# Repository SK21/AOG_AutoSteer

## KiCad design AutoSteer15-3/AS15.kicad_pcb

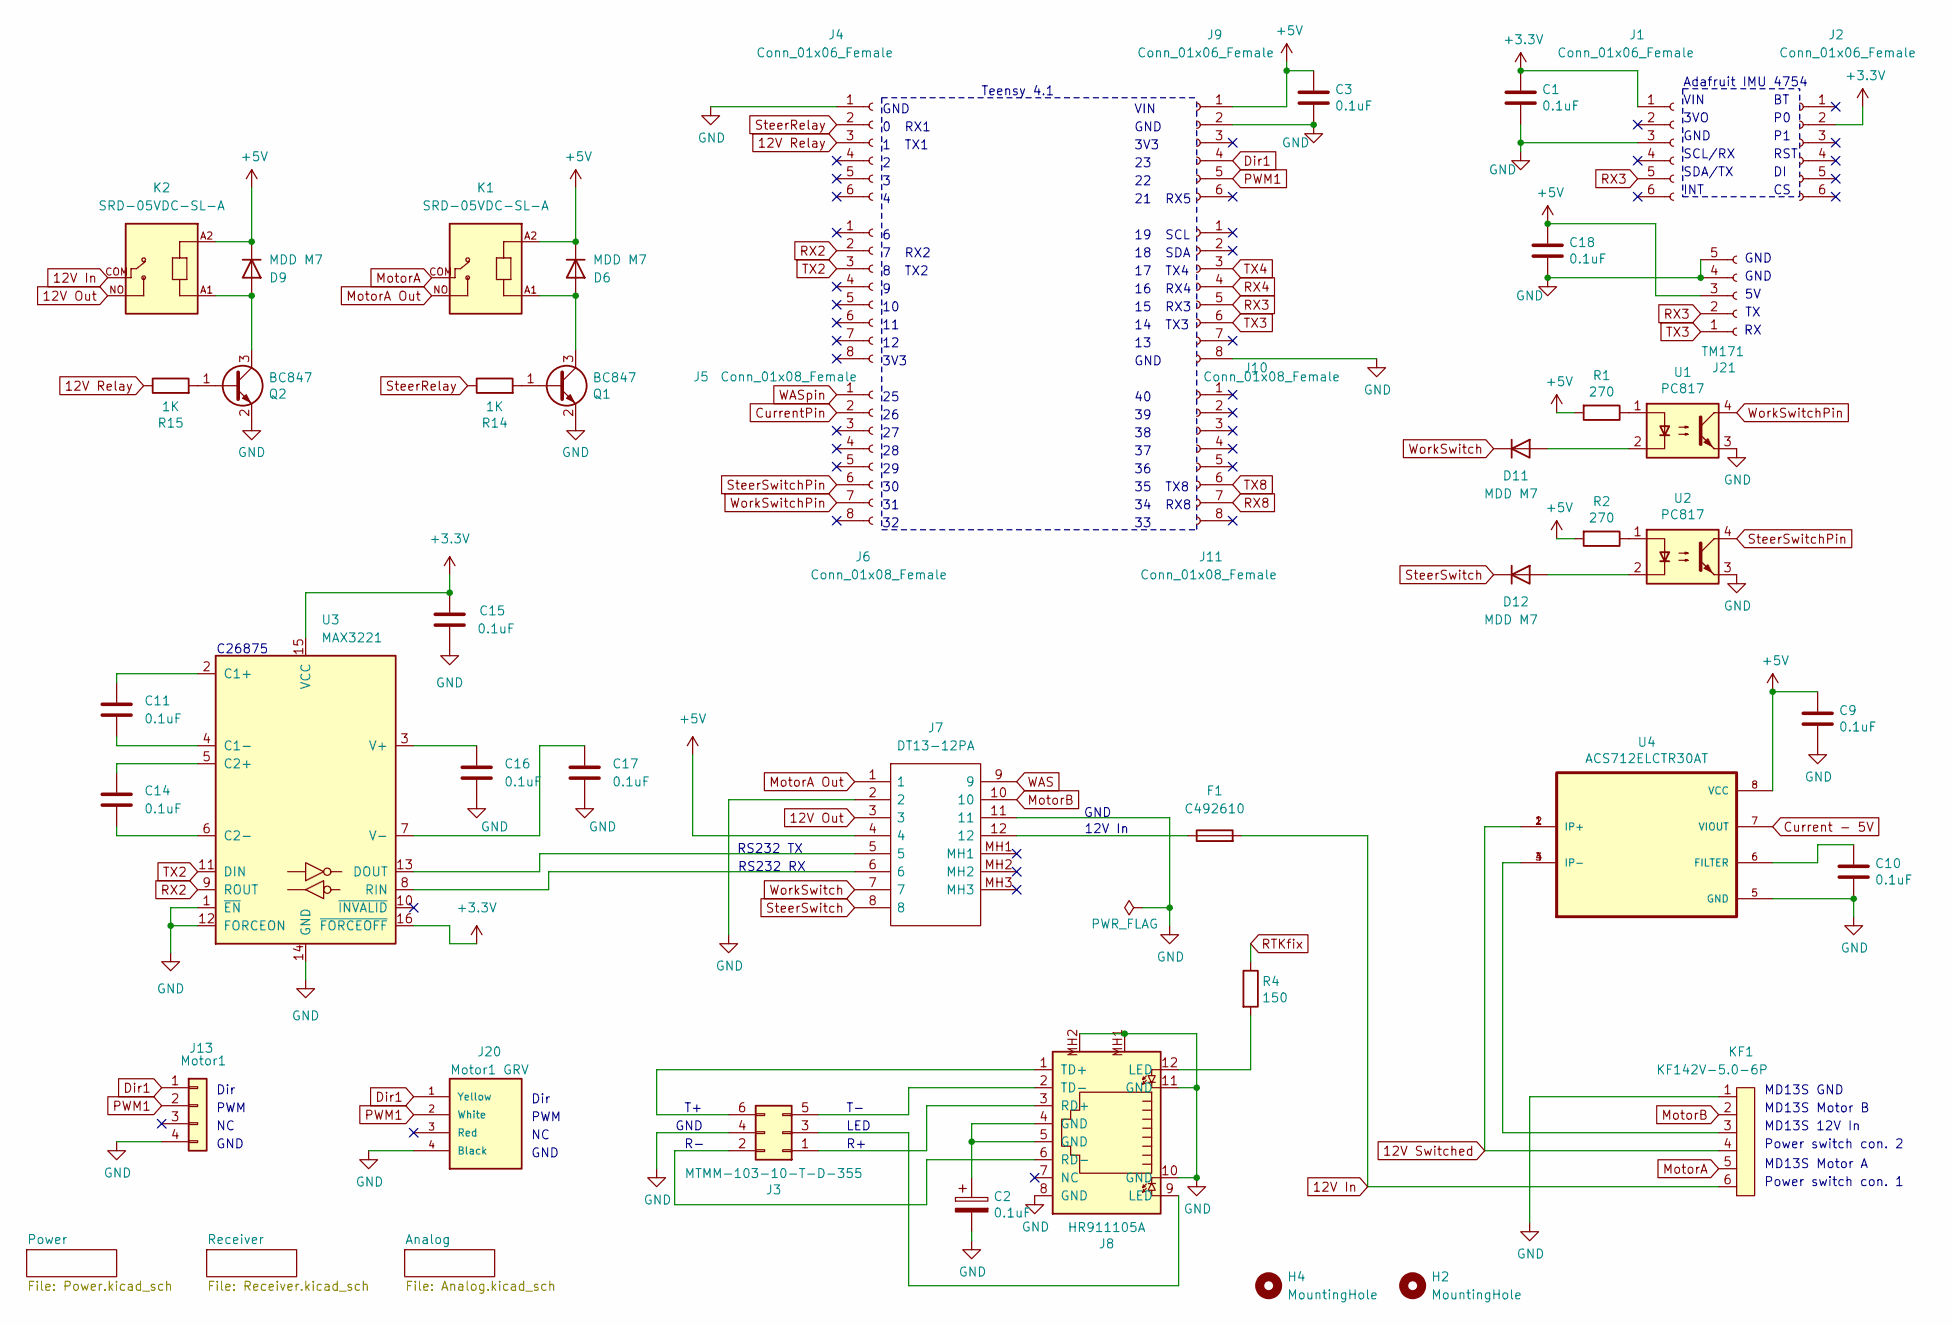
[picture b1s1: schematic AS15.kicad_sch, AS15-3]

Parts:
C1, C2, C3, C9, C10, C11, C14, C15, C16, C17, C18: 0.1uF; C_0805_2012Metric
D6, D9, D11, D12: MDD M7; D_SMA
F1: C492610; Fuse_Holder_C492610
H2, H4: MountingHole; MountingHole_4.3mm_M4
J1, J2, J4, J9: Conn_01x06_Female; PinSocket_1x06_P2.54mm_Vertical
J3: MTMM-103-10-T-D-355; PinHeader_2x03_P2.00mm_Vertical
J5, J6, J10, J11: Conn_01x08_Female; PinSocket_1x08_P2.54mm_Vertical
J7: DT13-12PA; DT1312PA; Manufacturer_Part_Number DT13-12PA; Mouser Part Number 571-DT13-12PA
J8: HR911105A
J13: Motor1; Molex_KK-254_AE-6410-04A_1x04_P2.54mm_Vertical
J20: Motor1 GRV; Grove
J21: TM171; PinSocket_1x05_P2.54mm_Vertical
K1, K2: SRD-05VDC-SL-A; RELAY_SRD-05VDC-SL-A
KF1: KF142V-5.0-6P; KF142V-5.08-6P
Q1, Q2: BC847; SOT-23
R1, R2: 270; R_0603_1608Metric
R4: 150; R_0603_1608Metric
R14, R15: 1K; R_0603_1608Metric
U1, U2: PC817; SMD-4_4.6x7.62mm_P2.54mm
U3: MAX3221; SOP65P777X199-16N
U4: ACS712ELCTR30AT; SOIC127P600X175-8N; PARTREV 1.0

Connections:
12V In: F1.2, K2.COM, KF1.6
12V Out: J7.3, K2.NO
12V Relay: J4.3, R15.1
12V Switched: KF1.4, U4.1 (IP+), U4.2 (IP+); also elsewhere on the board
+3.3V: C1.1, C15.1, J1.1, J2.2, U3.15 (VCC), U3.16 (~FORCEOFF); also elsewhere on the board
+5V: C3.1, C9.1, C18.1, D6.1 (K), D9.1 (K), J7.4, J9.1, J21.3, K1.A2, K2.A2, R1.2, R2.2, U4.8 (VCC); also elsewhere on the board
Current - 5V: U4.7 (VIOUT); also elsewhere on the board
CurrentPin: J6.2; also elsewhere on the board
Dir1: J9.4, J13.1, J20.1 (Yellow)
GND: C1.2, C2.2, C3.2, C9.2, C10.2, C15.2, C16.2, C17.2, C18.2, J1.3, J3.4, J4.1, J7.2, J7.11, J8.8 (GND), J8.10 (GND), J8.11 (GND), J8.MH1, J8.MH2, J9.2, J10.8, J13.4, J20.4 (Black), J21.4, J21.5, KF1.1, Q1.2 (E), Q2.2 (E), U1.3, U2.3, U3.1 (~EN), U3.12 (FORCEON), U3.14 (GND), U4.5 (GND); also elsewhere on the board
MotorA: K1.COM, KF1.5
MotorA Out: J7.1, K1.NO
MotorB: J7.10, KF1.2
unnamed: C2.1, J8.4 (GND), J8.5 (GND)
unnamed: D6.2 (A), K1.A1, Q1.3 (C)
unnamed: D9.2 (A), K2.A1, Q2.3 (C)
unnamed: D11.2 (A), U1.2
unnamed: D12.2 (A), U2.2
unnamed: F1.1, J7.12
unnamed: J3.1, J8.3 (RD+)
unnamed: J3.2, J8.6 (RD-)
unnamed: J3.3, J8.9 (LED)
unnamed: J3.5, J8.2 (TD-)
unnamed: J3.6, J8.1 (TD+)
unnamed: J8.12 (LED), R4.2
unnamed: KF1.3, U4.3 (IP-), U4.4 (IP-)
unnamed: Q1.1 (B), R14.2
unnamed: Q2.1 (B), R15.2
unnamed: R1.1, U1.1
unnamed: R2.1, U2.1
unnamed: C11.1, U3.2 (C1+)
unnamed: C11.2, U3.4 (C1-)
unnamed: C14.1, U3.5 (C2+)
unnamed: C14.2, U3.6 (C2-)
unnamed: J7.5, U3.13 (DOUT)
unnamed: J7.6, U3.8 (RIN)
unnamed: C16.1, U3.3 (V+)
unnamed: C17.1, U3.7 (V-)
unnamed: C10.1, U4.6 (FILTER)
PWM1: J9.5, J13.2, J20.2 (White)
RTKfix: R4.1; also elsewhere on the board
RX2: J5.2, U3.9 (ROUT)
RX3: J1.5, J10.5, J21.2
RX4: J10.4; also elsewhere on the board
RX8: J11.7; also elsewhere on the board
SteerRelay: J4.2, R14.1
SteerSwitch: D12.1 (K), J7.8
SteerSwitchPin: J6.6, U2.4
TX2: J5.3, U3.11 (DIN)
TX3: J10.6, J21.1
TX4: J10.3; also elsewhere on the board
TX8: J11.6; also elsewhere on the board
WAS: J7.9; also elsewhere on the board
WASpin: J6.1; also elsewhere on the board
WorkSwitch: D11.1 (K), J7.7
WorkSwitchPin: J6.7, U1.4

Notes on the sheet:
3V3
GND
RS232 TX
C26875
7 RX2
19 SCL
Teensy 4.1
MD13S Motor B
LED
8 TX2
35 TX8
Dir
16 RX4
SCL/RX
MD13S GND
14 TX3
VIN
17 TX4
RST
PWM
3VO
12V In
Power switch con. 1
MD13S Motor A
MD13S 12V In
34 RX8
Power switch con. 2
1 TX1
RS232 RX
18 SDA
INT
0 RX1
SDA/TX
21 RX5
15 RX3
Adafruit IMU 4754

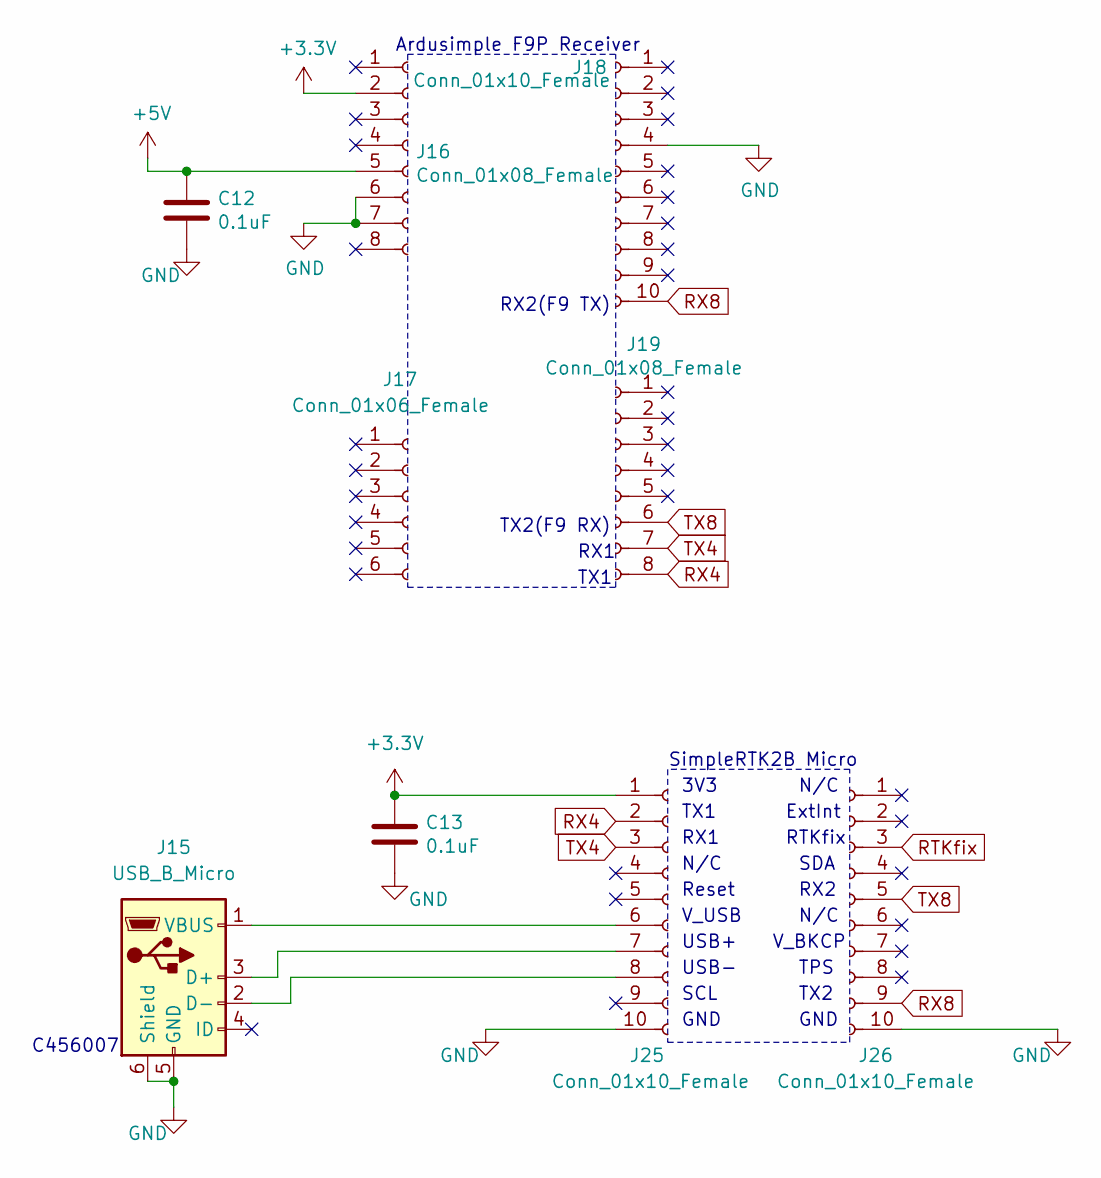
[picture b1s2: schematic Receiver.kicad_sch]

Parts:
C12, C13: 0.1uF; C_0805_2012Metric
J15: USB_B_Micro; USB_Micro-B_Wuerth_614105150721_Vertical
J16, J19: Conn_01x08_Female; PinSocket_1x08_P2.54mm_Vertical
J17: Conn_01x06_Female; PinSocket_1x06_P2.54mm_Vertical
J18: Conn_01x10_Female; PinSocket_1x10_P2.54mm_Vertical
J25, J26: Conn_01x10_Female; PinSocket_1x10_P2.00mm_Vertical

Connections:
+3.3V: C13.1, J16.2, J25.1; also elsewhere on the board
+5V: C12.1, J16.5; also elsewhere on the board
GND: C12.2, C13.2, J15.5 (GND), J15.6 (Shield), J16.6, J16.7, J18.4, J25.10, J26.10; also elsewhere on the board
unnamed: J15.3 (D+), J25.7
unnamed: J15.2 (D-), J25.8
unnamed: J15.1 (VBUS), J25.6
RTKfix: J26.3; also elsewhere on the board
RX4: J19.8, J25.2; also elsewhere on the board
RX8: J18.10, J26.9; also elsewhere on the board
TX4: J19.7, J25.3; also elsewhere on the board
TX8: J19.6, J26.5; also elsewhere on the board

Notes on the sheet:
RX1
3V3
TX1
SCL
RX2(F9 TX)
GND
N/C
USB-
TPS
SDA
TX2
V_USB
V_BKCP
RX2
C456007
ExtInt
Reset
Ardusimple F9P Receiver
SimpleRTK2B Micro
RTKfix
TX2(F9 RX)
USB+

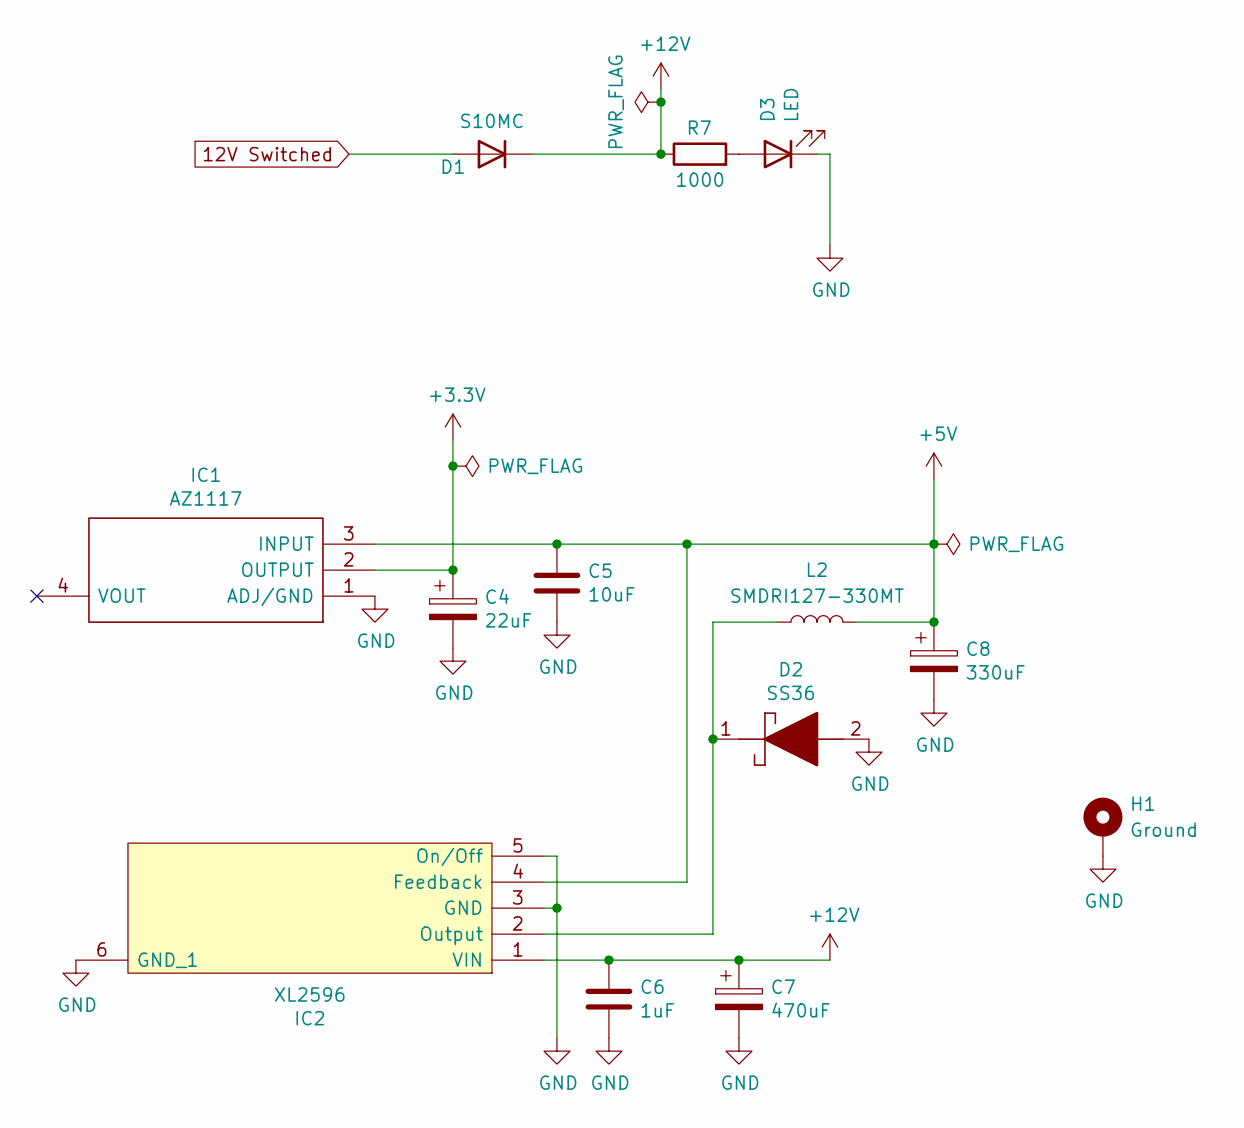
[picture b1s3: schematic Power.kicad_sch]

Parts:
C4: 22uF; C_0805_2012Metric
C5: 10uF; C_0805_2012Metric
C6: 1uF; C_0805_2012Metric
C7: 470uF; CP_Elec_10x10.5
C8: 330uF; CP_Elec_10x10.5
D1: S10MC; D_SMC_larger_pads
D2: SS36; SMA(DO-214AC)
D3: LED; LED_0805_2012Metric
H1: Ground; MountingHole_2.2mm_M2_DIN965_Pad
IC1: AZ1117; SOT-223
IC2: XL2596; TO263-5L
L2: SMDRI127-330MT; TMPA1265SP-101MN-D
R7: 1000; R_0603_1608Metric

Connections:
12V Switched: D1.2 (A); also elsewhere on the board
+3.3V: C4.1, IC1.2 (OUTPUT); also elsewhere on the board
+5V: C5.1, C8.1, IC1.3 (INPUT), IC2.4 (Feedback), L2.2; also elsewhere on the board
+12V: C6.1, C7.1, D1.1 (K), IC2.1 (VIN), R7.1
GND: C4.2, C5.2, C6.2, C7.2, C8.2, D2.2, D3.1 (K), H1.1, IC1.1 (ADJ/GND), IC2.3 (GND), IC2.5 (On/Off), IC2.6 (GND_1); also elsewhere on the board
unnamed: D3.2 (A), R7.2
unnamed: D2.1, IC2.2 (Output), L2.1

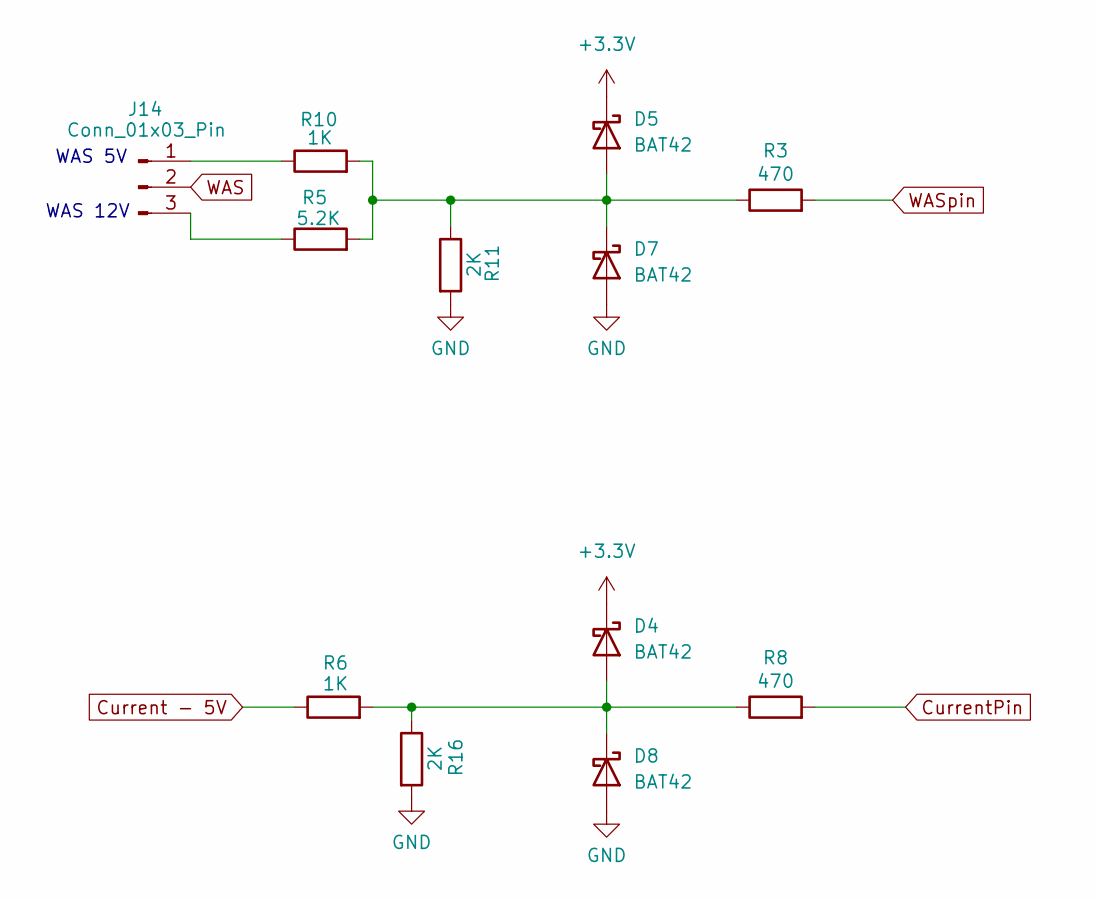
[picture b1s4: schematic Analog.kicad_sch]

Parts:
D4, D5, D7, D8: BAT42; D_SOD-123
J14: Conn_01x03_Pin; PinHeader_1x03_P2.54mm_Vertical
R3, R8: 470; R_0603_1608Metric
R5: 5.2K; R_0603_1608Metric
R6, R10: 1K; R_0603_1608Metric
R11, R16: 2K; R_0603_1608Metric

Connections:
+3.3V: D4.1 (K), D5.1 (K); also elsewhere on the board
Current - 5V: R6.1; also elsewhere on the board
CurrentPin: R8.2; also elsewhere on the board
GND: D7.2 (A), D8.2 (A), R11.2, R16.2; also elsewhere on the board
unnamed: D4.2 (A), D8.1 (K), R6.2, R8.1, R16.1
unnamed: D5.2 (A), D7.1 (K), R3.1, R5.2, R10.2, R11.1
unnamed: J14.1, R10.1
unnamed: J14.3, R5.1
WAS: J14.2; also elsewhere on the board
WASpin: R3.2; also elsewhere on the board

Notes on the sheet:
WAS 12V
WAS 5V

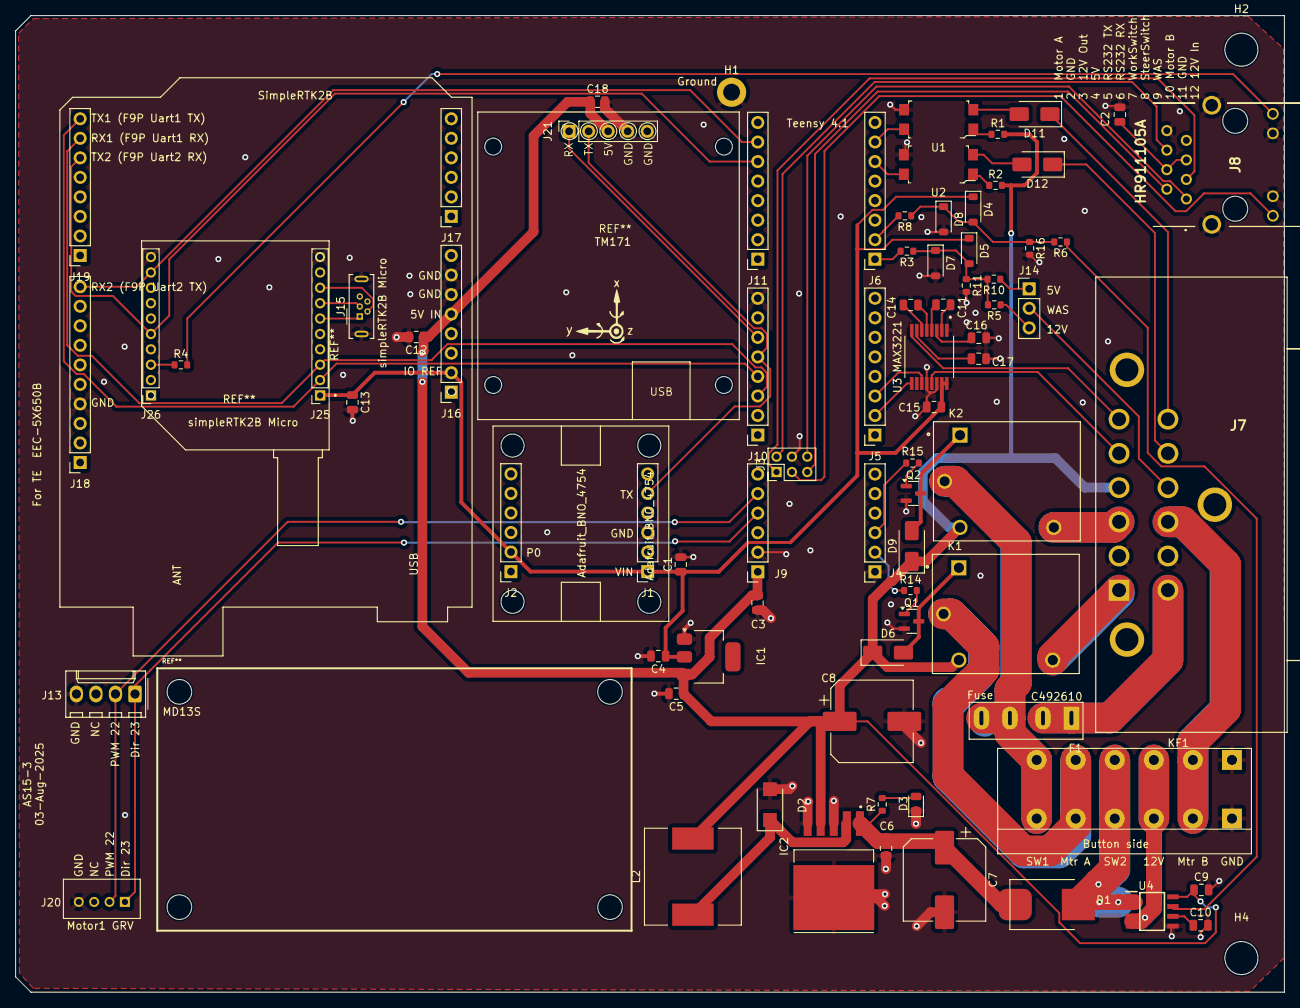
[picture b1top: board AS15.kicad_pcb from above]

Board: 2 copper layers, 165.0 x 127.0 mm, 80 parts (0 on the bottom side), 66 nets.

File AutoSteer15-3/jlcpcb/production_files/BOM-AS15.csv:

Comment,Designator,Footprint,LCSC,Quantity
ACS712ELCTR30AT,U4,SOIC127P600X175-8N,C10681,1
SS36,D2,SMA(DO-214AC),C116712,1
HR911105A,J8,HR911105A,C12074,1
150,R4,R_0603_1608Metric,C126805,1
BAT42,"D4,D5,D7,D8",D_SOD-123,C134396,4
SRD-05VDC-SL-A,"K1,K2",RELAY_SRD-05VDC-SL-A,C140615,2
10uF,C5,C_0805_2012Metric,C15850,1
S10MC,D1,D_SMC_larger_pads,C169472,1
330uF,C8,CP_Elec_10x10.5,C19606,1
1K,"R10,R14,R15,R6,R7",R_0603_1608Metric,C21190,5
270,"R1,R2",R_0603_1608Metric,C22966,2
2K,"R11,R16",R_0603_1608Metric,C22975,2
5.2K,R5,R_0603_1608Metric,C23068,1
470,"R3,R8",R_0603_1608Metric,C23179,2
MAX3221,U3,SOP65P777X199-16N,C26875,1
Conn_01x08_Female,"J10,J11,J16,J19,J5,J6",PinSocket_1x08_P2.54mm_Vertical,C27438,6
1uF,C6,C_0805_2012Metric,C28323,1
Conn_01x10_Female,"J25,J26",PinSocket_1x10_P2.00mm_Vertical,C2925557,2
470uF,C7,CP_Elec_10x10.5,C402578,1
Motor1 GRV,J20,Grove,C403774,1
Conn_01x06_Female,"J1,J17,J2,J4,J9",PinSocket_1x06_P2.54mm_Vertical,C40877,5
USB_B_Micro,J15,USB_Micro-B_Wuerth_614105150721_Vertical,C456007,1
22uF,C4,C_0805_2012Metric,C45783,1
KF142V-5.0-6P,KF1,KF142V-5.08-6P,C475138,1
Conn_01x03_Pin,J14,PinHeader_1x03_P2.54mm_Vertical,C49257,1
C492610,F1,Fuse_Holder_C492610,C492610,1
0.1uF,"C1,C10,C11,C12,C13,C14,C15,C16,C17,C18,C2,C3,C9",C_0805_2012Metric,C49678,13
TM171,J21,PinSocket_1x05_P2.54mm_Vertical,C50950,1
Conn_01x10_Female,J18,PinSocket_1x10_P2.54mm_Vertical,C5116489,1
BC847,"Q1,Q2",SOT-23,C57668,2
PC817,"U1,U2",SMD-4_4.6x7.62mm_P2.54mm,C66405,2
XL2596,IC2,TO263-5L,C74190,1
LED,D3,LED_0805_2012Metric,C84256,1
Motor1,J13,Molex_KK-254_AE-6410-04A_1x04_P2.54mm_Vertical,C86504,1
AZ1117,IC1,SOT-223,C92517,1
SMDRI127-330MT,L2,TMPA1265SP-101MN-D,C9400,1
MDD M7,"D11,D12,D6,D9",D_SMA,C95872,4
DT13-12PA,J7,DT1312PA,,1
Teensy_Ethernet,J3,PinHeader_2x03_P2.00mm_Vertical,,1

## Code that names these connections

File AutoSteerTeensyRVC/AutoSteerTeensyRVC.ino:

#include <Wire.h>
#include <EEPROM.h> 
#include <NativeEthernet.h>
#include <NativeEthernetUdp.h>

#include "zNMEAParser.h"	
#include "Adafruit_BNO08x_RVC.h"	// https://github.com/VikingVoltage/Adafruit_BNO08x_RVC/tree/Get-most-recent-BNO08x-Data-from-Serial-Buffer

#include "FXUtil.h"		// read_ascii_line(), hex file support
extern "C" {
#include "FlashTxx.h"		// TLC/T3x/T4x/TMM flash primitives
}

// autosteer for Teensy 4.1
// uses BNO in RVC mode over serial

#include <Adafruit_Sensor.h>
#define InoDescription "AutoSteerTeensyRVC"
const uint16_t InoID = 6085;	// change to send defaults to eeprom, ddmmy, no leading 0
const uint8_t InoType = 0;		// 0 - Teensy AutoSteer, 1 - Teensy Rate, 2 - Nano Rate, 3 - Nano SwitchBox, 4 - ESP Rate
const int16_t ADS1115_Address = 0x48;

#define ReceiverBaud 460800
#define IMUBaud 115200
#define MaxReadBuffer 100		// bytes
#define LOW_HIGH_DEGREES 5.0	// How many degrees before decreasing Max PWM
#define NC 0xFF					// Pin not connected
#define PassThruBaud 57600		// for RS232
#define NtripPort 2233			// local port to listen on for NTRIP data

struct ModuleConfig
{
	//	AS15-3 config
	uint8_t ReceiverSerialPort = 8;	
	uint8_t	IMUSerialPort = 3;	
	uint8_t PassThruInSerialPort = 4;		// from F9P Uart2
	uint8_t PassThrOutSerialPort = 2;		// to Max232 for DB9 connector
	uint8_t PowerRelayPin = 0;
	uint8_t SteeringRelayPin = 1;	// pin for steering disconnect relay
	uint8_t WasPin = 25;
	uint8_t CurrentPin = 26;
	uint8_t SteerSwitchPin = 30;
	uint8_t WorkSwitchPin = 31;
	uint8_t DirPin = 23;
	uint8_t PWMpin = 22;
	int16_t ZeroOffset = 0;
	bool InvertRoll = false;
	bool ADS1115Enabled = false;
	uint8_t IP0 = 192;
	uint8_t IP1 = 168;
	uint8_t IP2 = 1;
	uint8_t IP3 = 126;
};

ModuleConfig MDL;

struct Storage 
{
	uint8_t Kp = 40;  //proportional gain
	uint8_t lowPWM = 10;  //band of no action
	int16_t wasOffset = 0;
	uint8_t minPWM = 9;
	uint8_t highPWM = 60;//max PWM value
	float steerSensorCounts = 30;
	float AckermanFix = 1;     //sent as percent
};  

Storage SteerSettings;  //11 bytes

struct Setup
{
	uint8_t InvertWAS = 0;
	uint8_t InvertRelays = 0;	//if zero, active low (default)
	uint8_t InvertSteer = 0;
	uint8_t SingleInputWAS = 1;
	uint8_t CytronDriver = 1;
	uint8_t SteerSwitch = 0;	//1 if switch selected
	uint8_t SteerButton = 0;	//1 if button selected
	uint8_t ShaftEncoder = 0;
	uint8_t PressureSensor = 0;
	uint8_t CurrentSensor = 0;
	uint8_t PulseCountMax = 5;
	uint8_t IsDanfoss = 0;
	uint8_t UseIMU_Y_Axis = 0;	//Set to 0 to use X Axis, 1 to use Y avis
	double MinSpeed = 0;		// minimum kmh X 10
};

Setup SteerConfig;          //9 bytes

// Ethernet steering
EthernetUDP UDPsteering;	// UDP Steering traffic, to and from AGIO
uint16_t ListeningPort = 8888;
uint16_t DestinationPort = 9999;	// port that AGIO listens on
IPAddress DestinationIP(MDL.IP0, MDL.IP1, MDL.IP2, 255);

EthernetUDP UDPntrip;	// from AGIO to receiver
char NtripBuffer[512];	// buffer for ntrip data

// Ethernet config
EthernetUDP UDPconfig;
uint16_t ConfigListeningPort = 28888;
uint16_t ConfigDestinationPort = 29999;

//steering variables
float steerAngleActual = 0;
float steerAngleSetPoint = 0; //the desired angle from AgOpen
float steerAngleError = 0; //setpoint - actual
float Speed_KMH = 0.0;
int8_t guidanceStatus;

float IMU_Heading = 0;
float IMU_Roll = 0;
float IMU_Pitch = 0;
float IMU_YawRate = 0;

// switches
int8_t SteerSwitch = LOW;	// Low on, High off
int8_t switchByte = 0;
float SensorReading;

//pwm variables
int16_t pwmDrive = 0;
int16_t MaxPWMvalue = 255;

//Heart beat hello AgIO
uint8_t helloFromIMU[] = { 128, 129, 121, 121, 5, 0, 0, 0, 0, 0, 71 };
uint8_t helloFromAutoSteer[] = { 128, 129, 126, 126, 5, 0, 0, 0, 0, 0, 71 };
int16_t helloSteerPosition = 0;

//fromAutoSteerData FD 253 - ActualSteerAngle*100 -5,6, SwitchByte-7, pwmDisplay-8
uint8_t PGN_253[] = { 128, 129, 123, 253, 8, 0, 0, 0, 0, 0,0,0,0, 12 };

//fromAutoSteerData FD 250 - sensor values etc
uint8_t PGN_250[] = { 128, 129, 123, 250, 8, 0, 0, 0, 0, 0,0,0,0, 12 };

const uint16_t  LOOP_TIME = 25;	// 40 hz, main loop
uint32_t  LoopLast = LOOP_TIME;

NMEAParser<2> parser;
Adafruit_BNO08x_RVC rvc = Adafruit_BNO08x_RVC();
BNO08x_RVC_Data heading;

uint32_t AOGTime;
uint32_t NtripTime;

int16_t WasReading;
int16_t CurrentReading;
bool ADSfound = false;
byte PGNlength;

HardwareSerial* SerialIMU;
HardwareSerial* SerialReceiver;
HardwareSerial* SerialPassIn;
HardwareSerial* SerialPassOut;

elapsedMillis imuDelayTimer;
bool isGGA_Updated = false;

byte DataConfig[MaxReadBuffer];
uint16_t PGNconfig;

bool IMUstarted = false;

// firmware update
EthernetUDP UpdateComm;
uint16_t UpdateReceivePort = 29100;
uint16_t UpdateSendPort = 29000;
uint32_t buffer_addr, buffer_size;
bool UpdateMode = false;

//******************************************************************************
// hex_info_t struct for hex record and hex file info
//******************************************************************************
typedef struct {  //
	char* data;   // pointer to array allocated elsewhere
	unsigned int addr;  // address in intel hex record
	unsigned int code;  // intel hex record type (0=data, etc.)
	unsigned int num; // number of data bytes in intel hex record

	uint32_t base;  // base address to be added to intel hex 16-bit addr
	uint32_t min;   // min address in hex file
	uint32_t max;   // max address in hex file

	int eof;    // set true on intel hex EOF (code = 1)
	int lines;    // number of hex records received
} hex_info_t;

static char data[16];// buffer for hex data

hex_info_t hex =
{ // intel hex info struct
  data, 0, 0, 0,        //   data,addr,num,code
  0, 0xFFFFFFFF, 0,     //   base,min,max,
  0, 0					//   eof,lines
};

void setup()
{
	DoSetup();
}

void loop()
{
	if (millis() - LoopLast >= LOOP_TIME)
	{
		LoopLast = millis();
		ReadAnalog();
		ReadSwitches();
		DoSteering();
		ReceiveConfig();
	}
	ReadIMU();
	DoPanda();
	ReceiveSteerData();
	ReceiveUpdate();
	Blink();
	if (SerialPassIn->available()) SerialPassOut->write(SerialPassIn->read());
}

bool State = false;
elapsedMillis BlinkTmr;
byte ResetRead;
elapsedMicros LoopTmr;
uint32_t MaxLoopTime;
uint16_t debug1;

void Blink()
{
	if (BlinkTmr > 1000)
	{
		BlinkTmr = 0;
		State = !State;
		digitalWrite(LED_BUILTIN, State);
		if (!UpdateMode)
		{
			Serial.print(" Micros: ");
			Serial.print(MaxLoopTime);

			Serial.print(", WAS: ");
			Serial.print(helloSteerPosition);

			Serial.print(", Heading: ");
			Serial.print(IMU_Heading / 10.0);

			//Serial.print(", ");
			//Serial.print(debug1);

			Serial.println("");

			if (ResetRead++ > 5)
			{
				MaxLoopTime = 0;
				ResetRead = 0;
			}
		}
	}
	if (LoopTmr > MaxLoopTime) MaxLoopTime = LoopTmr;
	LoopTmr = 0;
}

bool GoodCRC(byte Data[], byte Length)
{
	byte ck = CRC(Data, Length - 1, 0);
	bool Result = (ck == Data[Length - 1]);
	return Result;
}

byte CRC(byte Chk[], byte Length, byte Start)
{
	byte Result = 0;
	int CK = 0;
	for (int i = Start; i < Length; i++)
	{
		CK += Chk[i];
	}
	Result = (byte)CK;
	return Result;
}

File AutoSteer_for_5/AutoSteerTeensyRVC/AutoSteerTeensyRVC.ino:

#define InoDescription "AutoSteerTeensyRVC   30-Apr-2023"
// autosteer for Teensy 4.1
// uses BNO in RVC mode over serial

#define InoID 3004	// if not in eeprom, overwrite

#include <Wire.h>
#include <EEPROM.h> 
#include <NativeEthernet.h>
#include <NativeEthernetUdp.h>
#include <Watchdog_t4.h>	// https://github.com/tonton81/WDT_T4
#include "zNMEAParser.h"	
#include "Adafruit_BNO08x_RVC.h"

#define ReceiverBaud 460800
#define IMUBaud 115200
#define MaxReadBuffer 100	// bytes
#define LOW_HIGH_DEGREES 5.0	//How many degrees before decreasing Max PWM
#define ADS1115_Address 0x48

struct ModuleConfig	
{
	uint8_t Receiver = 1;			// 0 none, 1 SimpleRTK2B, 2 Sparkfun F9p
	uint8_t ReceiverSerialPort = 4;	// GPS receiver
	uint8_t	IMUSerialPort = 7;		// IMU
	uint16_t NtripPort = 2233;		// local port to listen on for NTRIP data
	uint16_t ZeroOffset = 6500;
	uint8_t MinSpeed = 1;
	uint8_t MaxSpeed = 15;
	uint16_t PulseCal = 255;		// Hz/KMH X 10
	uint8_t	AnalogMethod = 2;		// 0 use ADS1115 for WAS(AIN0), AIN1, current(AIN2), 1 use Teensy analog pin for WAS, 2 use ADS1115 from Wemos D1 Mini
	uint8_t SwapRollPitch = 0;		// 0 use roll value for roll, 1 use pitch value for roll
	uint8_t InvertRoll = 0;
	uint8_t Dir1 = 26;
	uint8_t PWM1 = 25;
	uint8_t SteerSw_Relay = 36;		// pin for steering disconnect relay
	uint8_t SteerSw = 39;
	uint8_t WorkSw = 27;
	uint8_t CurrentSensor = 10;
	uint8_t PressureSensor = 26;
	uint8_t Encoder = 38;
	uint8_t SpeedPulse = 37;
	uint8_t IP0 = 192;
	uint8_t IP1 = 168;
	uint8_t IP2 = 1;
	uint8_t IP3 = 126;
};

ModuleConfig MDL;

struct PCBanalog
{
	int16_t AIN0;	// WAS
	int16_t AIN1;	// linear actuator position or pressure sensor
	int16_t AIN2;	// current sensor
	int16_t AIN3;
};

PCBanalog AINs;

struct Storage 
{
	uint8_t Kp = 40;  //proportional gain
	uint8_t lowPWM = 10;  //band of no action
	int16_t wasOffset = 0;
	uint8_t minPWM = 9;
	uint8_t highPWM = 60;//max PWM value
	float steerSensorCounts = 30;
	float AckermanFix = 1;     //sent as percent
};  

Storage steerSettings;  //11 bytes

struct Setup
{
	uint8_t InvertWAS = 0;
	uint8_t IsRelayActiveHigh = 0; //if zero, active low (default)
	uint8_t MotorDriveDirection = 0;
	uint8_t SingleInputWAS = 1;
	uint8_t CytronDriver = 1;
	uint8_t SteerSwitch = 0;  //1 if switch selected
	uint8_t SteerButton = 0;  //1 if button selected
	uint8_t ShaftEncoder = 0;
	uint8_t PressureSensor = 0;
	uint8_t CurrentSensor = 0;
	uint8_t PulseCountMax = 5;
	uint8_t IsDanfoss = 0;
	uint8_t IsUseY_Axis = 0;     //Set to 0 to use X Axis, 1 to use Y avis
};

Setup steerConfig;          //9 bytes

// Ethernet steering
EthernetUDP UDPsteering;	// UDP Steering traffic, to and from AGIO
uint16_t ListeningPort = 8888;
uint16_t DestinationPort = 9999;	// port that AGIO listens on
IPAddress DestinationIP(MDL.IP0, MDL.IP1, MDL.IP2, 255);

// Ethernet switchbox
EthernetUDP UDPswitches;
uint16_t ListeningPortSwitches = 28888;
uint16_t DestinationPortSwitches = 29999;

EthernetUDP UDPntrip;	// from AGIO to receiver
char NtripBuffer[512];	// buffer for ntrip data

//steering variables
float steerAngleActual = 0;
float steerAngleSetPoint = 0; //the desired angle from AgOpen
int16_t steeringPosition = 0;
float steerAngleError = 0; //setpoint - actual
float Speed_KMH = 0.0;
int8_t guidanceStatus;

float IMU_Heading = 0;
float IMU_Roll = 0;
float IMU_Pitch = 0;
float IMU_YawRate = 0;

// switches
int8_t SteerSwitch = LOW;	// Low on, High off
int8_t SWreading = HIGH;
int8_t SWprevious = LOW;
uint32_t  SWtime = 0;
uint8_t  SWdebounce = 50;
int8_t switchByte = 0;
int8_t workSwitch = 0;
float SensorReading;

//pwm variables
int16_t pwmDrive = 0;
int16_t MaxPWMvalue = 255;

//Heart beat hello AgIO
uint8_t helloFromIMU[] = { 128, 129, 121, 121, 5, 0, 0, 0, 0, 0, 71 };
uint8_t helloFromAutoSteer[] = { 128, 129, 126, 126, 5, 0, 0, 0, 0, 0, 71 };
int16_t helloSteerPosition = 0;

//fromAutoSteerData FD 253 - ActualSteerAngle*100 -5,6, SwitchByte-7, pwmDisplay-8
uint8_t PGN_253[] = { 128, 129, 123, 253, 8, 0, 0, 0, 0, 0,0,0,0, 12 };

//fromAutoSteerData FD 250 - sensor values etc
uint8_t PGN_250[] = { 128, 129, 123, 250, 8, 0, 0, 0, 0, 0,0,0,0, 12 };

WDT_T4<WDT1> wdt;
const uint16_t  LOOP_TIME = 25;	// 40 hz, main loop
uint32_t  LoopLast = LOOP_TIME;

NMEAParser<2> parser;
Adafruit_BNO08x_RVC rvc = Adafruit_BNO08x_RVC();
BNO08x_RVC_Data heading;

uint32_t CommTime;
bool ADSfound = false;
byte PGNlength;

HardwareSerial* SerialIMU;
HardwareSerial* SerialReceiver;

extern float tempmonGetTemp(void);
elapsedMillis imuDelayTimer;
bool isGGA_Updated = false;

void setup()
{
	DoSetup();
}

void loop()
{
	if (millis() - LoopLast >= LOOP_TIME)
	{
		LoopLast = millis();
		ReadAnalog();
		ReadSwitches();
		DoSteering();
		SendSpeedPulse();
		ReceiveConfigData();
	}
	ReadIMU();
	ReceiveSteerData();
	DoPanda();
	Blink();
	wdt.feed();
}

bool State = false;
elapsedMillis BlinkTmr;
byte ResetRead;
elapsedMicros LoopTmr;
uint32_t MaxLoopTime;
void Blink()
{
	if (BlinkTmr > 1000)
	{
		BlinkTmr = 0;
		State = !State;
		digitalWrite(LED_BUILTIN, State);
		Serial.println(".");	// needed to allow PCBsetup to connect

		Serial.print(" Loop Time (Micros): ");
		Serial.print(MaxLoopTime);

		Serial.print(", WAS: ");
		Serial.print(AINs.AIN0);

		Serial.print(", Heading: ");
		Serial.print(IMU_Heading / 10.0);

		//Serial.print(", Temp: ");
		//Serial.print(tempmonGetTemp());

		Serial.println("");

		if (ResetRead++ > 5)
		{
			MaxLoopTime = 0;
			ResetRead = 0;
		}
	}
	if (LoopTmr > MaxLoopTime) MaxLoopTime = LoopTmr;
	LoopTmr = 0;
}

uint32_t SpeedPulseTime;
void SendSpeedPulse()
{
	// https://discourse.agopengps.com/t/get-feed-rate-from-ago-and-transform-it-into-weedkiller-sprayer-computer-compatible-pulses/2958/39
	// PulseCal: hz/mph - 41.0, hz/kmh - 25.5

	if (millis() - SpeedPulseTime > 400) //This section runs every 400 millis.  It gets speed and changes the frequency of the tone generator.
	{
		SpeedPulseTime = millis();
		if (Speed_KMH < 1.22) // If the speed is lower than (0.76 MPH, 1.22 KMH) or (31.1 Hz) it forces the output to 0. Tone will not work under 31 Hz 
		{
			noTone(MDL.SpeedPulse);
		}
		else
		{
			tone(MDL.SpeedPulse, (Speed_KMH * MDL.PulseCal / 10));
		}
	}
}

bool GoodCRC(byte Data[], byte Length)
{
	byte ck = CRC(Data, Length - 1, 0);
	bool Result = (ck == Data[Length - 1]);
	return Result;
}

byte CRC(byte Chk[], byte Length, byte Start)
{
	byte Result = 0;
	int CK = 0;
	for (int i = Start; i < Length; i++)
	{
		CK += Chk[i];
	}
	Result = (byte)CK;
	return Result;
}

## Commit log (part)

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2021-03-15 autosteer for 4.3
2023-04-19 add gitignore
2023-04-19 Move autosteer files
2023-04-19 Revert "Move autosteer files"
    This reverts commit 403095b6362e134b2a8abf9891f1a796aca93ff4.
2023-04-19 Added steering modules for AOG 5
2023-04-21 added PinOut
2023-04-24 create BNO RVC version
2023-04-25 remove wemos, cmps14
2023-04-29 adjust timing
2023-04-30 update panda, remove usb host
2023-04-30 code cleanup, add Power Relay
2023-04-30 changed folders
2023-07-01 update for AS15
2023-07-03 update pins for AS15, fix analog, fix pressure sensor
2023-07-03 add AS15 pcb
2023-07-03 update folders
2023-07-03 added pictures
2023-07-03 update hex file
2023-07-24 add MCP and PCA for relays
2023-07-31 update settings for AS14 pcb
2023-08-01 add more pictures
2023-08-17 config over udp
2023-08-18 fix relays
2023-09-29 add settings
2023-10-07 config pgns, module info
2023-12-30 update config pgns
2023-12-30 fix config
2023-12-31 add ino type
2024-01-21 update switch code
2024-01-22 update analog
2024-01-25 remove files
2024-02-19 update pgns, validate pins
2024-02-21 fix ValidData sub
2024-02-21 add micro note
2024-02-24 update receiver serial port
2024-02-25 update micro connection, relay types
2024-03-06 add pgn32503
2024-04-22 UDP send F9P Uart2
2024-06-05 add ethernet update
2025-03-08 AS15-2 initial
2025-03-08 Testing
2025-03-10 clean up
2025-03-10 change bno library
2025-07-20 change version #
2025-07-23 Revert "change version #"
    This reverts commit e879a3827e5b329a56d8bb46ea690d67678a2326.
2025-07-23 change version display format
2025-08-01 AS15-3 changes
2025-08-01 update module variables
2025-08-06 move swap pitch roll to SteerConfig
2025-08-06 add TM171 imu
2025-08-06 add ADS1115 address
2025-08-06 IMU config
2025-08-06 add imu url
2025-08-07 use while in the TM171 code
2025-08-10 code cleanup
2025-08-10 serial port check
2025-08-10 auto zero was
2025-08-11 update pgn pdf
2025-08-11 max reads for TM171 imu
2025-08-11 fix SetSerialPort, add pressure
2025-08-12 add status pgn
2025-08-13 fix steer switches
2025-08-14 add shaftencoder
2025-08-18 add speed pulse, update switches
2025-08-18 use speedkmh
2025-08-19 add current was to status
2025-08-19 update ADS
2025-08-19 update hex
2025-08-20 Change ADS scaling. Remove median calculation.
2025-08-21 use float
2025-09-12 revert to previous analog read
2025-09-14 change version display
2025-09-20 fix defaults, network struct
2025-09-20 virtual encoder
2025-10-07 remove old code
2025-10-11 average was reading
2025-10-21 change tm171 code
2025-10-21 remove invert roll, handled by aog
2025-10-25 increase WAS read rate
2025-10-25 update autozerowas
2025-10-31 increase ntrip buffer size
2026-04-29 change pwm frequency, fix build errors
2026-04-29 update autozero was
2026-05-10 add UM982 and tool steer support
2026-05-10 update ksxt parsing
2026-05-10 HPR version
2026-05-10 use pashr sentence
2026-05-10 rebuild project
2026-05-11 match ToolDual
2026-05-11 bynav config
